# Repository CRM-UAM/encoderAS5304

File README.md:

# encoderAS5304
PCB para los encoders magnéticos (sensores hall AS5304 + Anillo magnético AS5000-MR20-44)

Alimentación a 5V

Salida: doble señal de cuadratura con los canales A y B

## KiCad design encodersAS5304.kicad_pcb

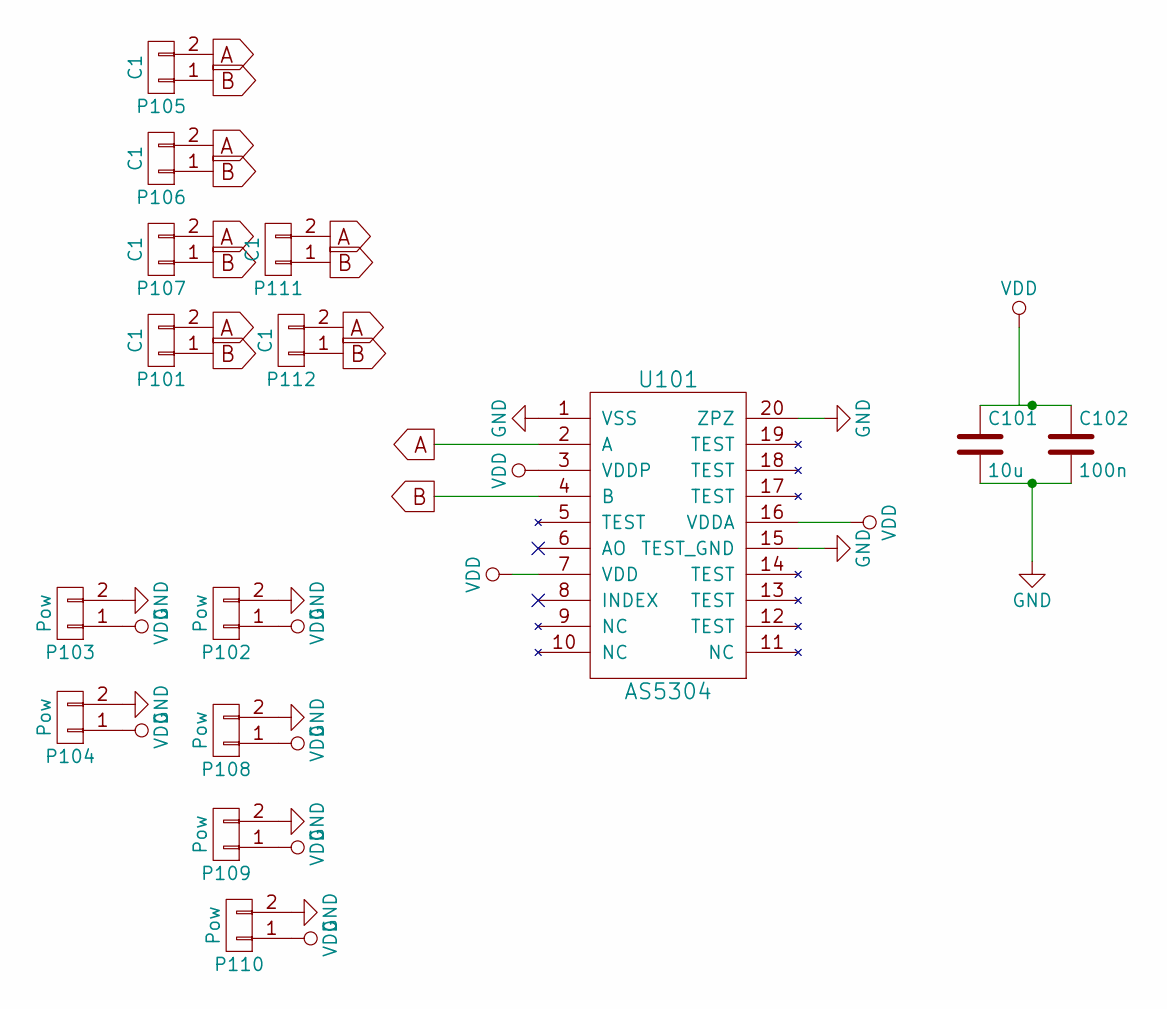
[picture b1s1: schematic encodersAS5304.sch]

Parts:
C101: 10u; C_1210_HandSoldering
C102: 100n; C_1210_HandSoldering
P101, P105, P106, P107, P111, P112: C1; Pin_Header_Straight_1x02
P102, P103, P104, P108, P109, P110: Pow; Pin_Header_Straight_1x02
U101: AS5304; SSOP-20_4.4x6.5mm_Pitch0.65mm

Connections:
A: P101.2, P105.2, P106.2, P107.2, P111.2, P112.2, U101.2 (A)
B: P101.1, P105.1, P106.1, P107.1, P111.1, P112.1, U101.4 (B)
GND: C101.2, C102.2, P102.2, P103.2, P104.2, P108.2, P109.2, P110.2, U101.1 (VSS), U101.15 (TEST_GND), U101.20 (ZPZ)
VDD: C101.1, C102.1, P102.1, P103.1, P104.1, P108.1, P109.1, P110.1, U101.3 (VDDP), U101.7 (VDD), U101.16 (VDDA)

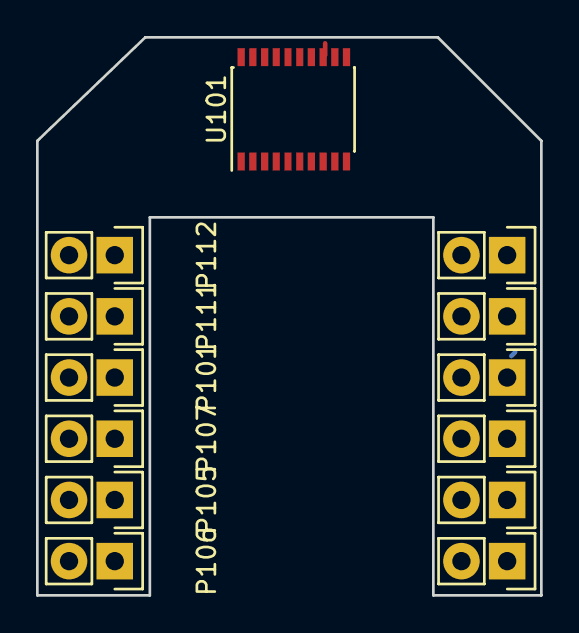
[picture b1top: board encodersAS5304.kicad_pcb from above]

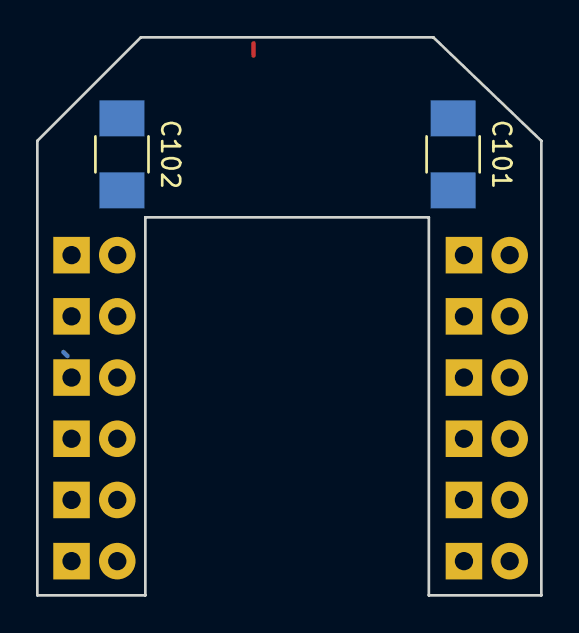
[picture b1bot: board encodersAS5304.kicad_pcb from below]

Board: 2 copper layers, 28.0 x 31.0 mm, 15 parts (2 on the bottom side), 4 nets.

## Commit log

2016-11-11 comit inicial
2016-11-12 placa con forma apropiada y dimensiones exactas. Falta enrutado
2016-11-13 enrutada + plano de masa en las dos capas
2016-11-13 removed old files
2016-11-13 removed bak files
2016-11-13 imgs
2016-11-13 README imgs2
2016-11-13 README img
2016-11-13 rename imgs
2017-10-08 vias fuera de los componente + cambio de huella de los condensadores + serigrafia
